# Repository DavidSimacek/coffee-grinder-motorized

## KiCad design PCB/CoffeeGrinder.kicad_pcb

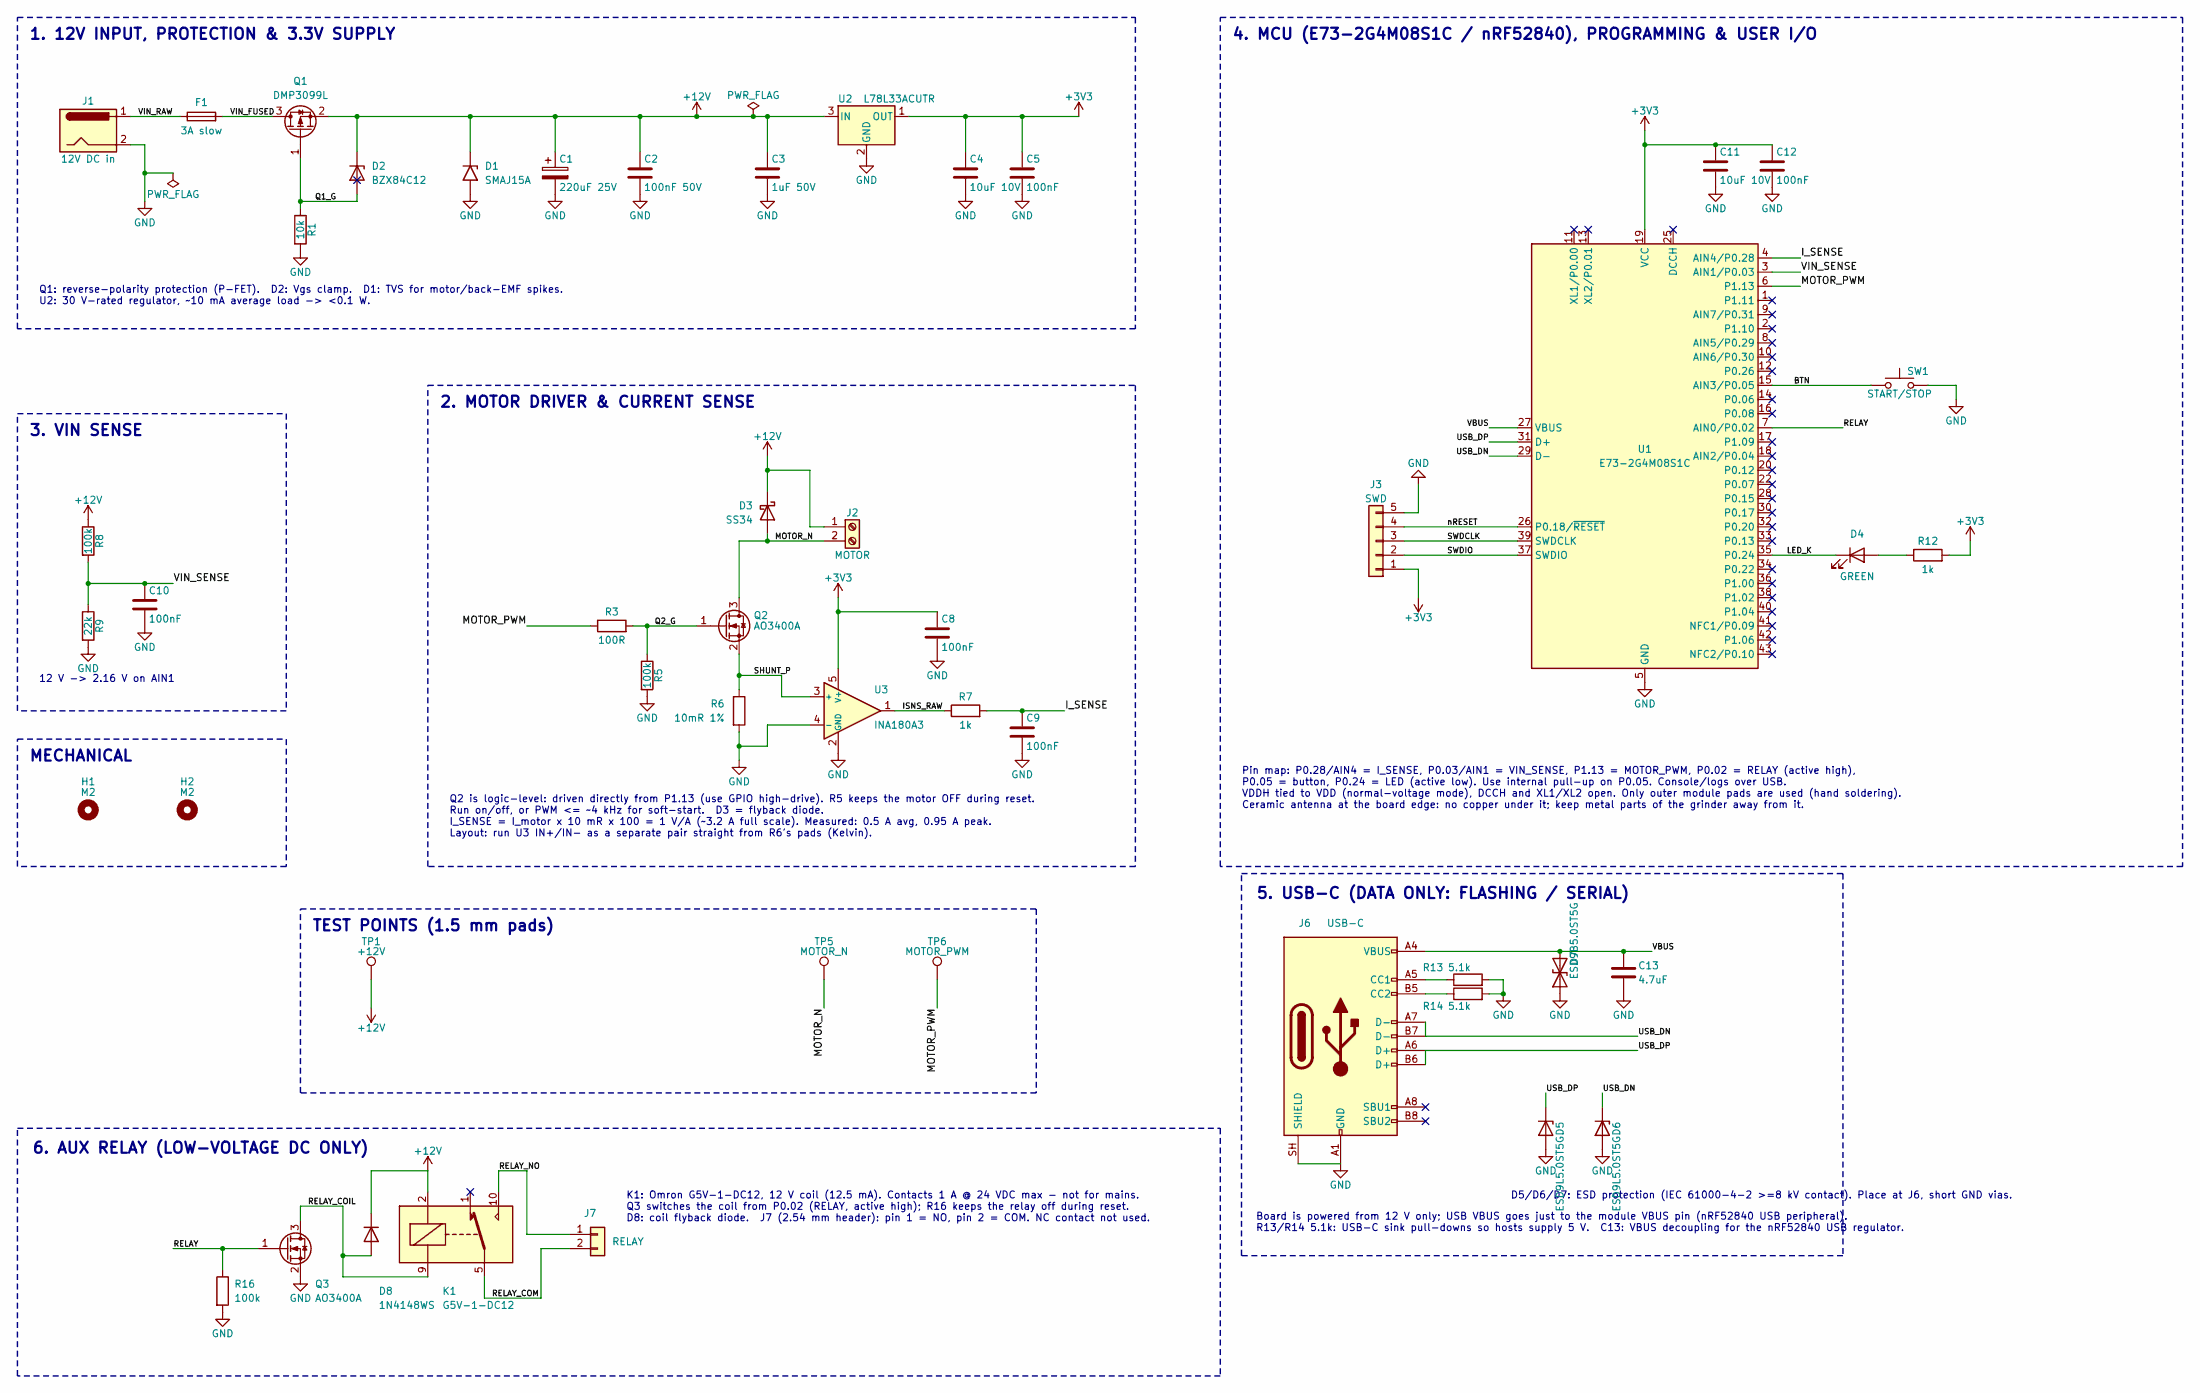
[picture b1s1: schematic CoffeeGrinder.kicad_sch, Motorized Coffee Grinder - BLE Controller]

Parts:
C1: 220uF 25V; CP_Radial_D6.3mm_P2.50mm
C2: 100nF 50V; C_0603_1608Metric
C3: 1uF 50V; C_0805_2012Metric
C4, C11: 10uF 10V; C_0805_2012Metric
C5, C8, C9, C10, C12: 100nF; C_0603_1608Metric
C13: 4.7uF; C_0603_1608Metric; LCSC C19666
D1: SMAJ15A; D_SMA
D2: BZX84C12; SOT-23
D3: SS34; D_SMA
D4: GREEN; LED_0603_1608Metric
D5, D6: ESD9L5.0ST5G; D_SOD-923_NoSilk; LCSC C82326
D7: ESD9B5.0ST5G; D_SOD-923_NoSilk; LCSC C111566
D8: 1N4148WS; D_SOD-323; LCSC C2128
F1: 3A slow; Fuse_1206_3216Metric; LCSC C41367225
H1, H2: M2; MountingHole_2.2mm_M2
J1: 12V DC in; BarrelJack_Horizontal
J2: MOTOR; TerminalBlock_Kefa_KF301-5.0-2P
J3: SWD; PinHeader_1x05_P2.54mm_Vertical
J6: USB-C; USB_C_HRO_TYPE-C-31-M-12_EdgeMount; LCSC C165948
J7: RELAY; PinHeader_1x02_P2.54mm_Vertical
K1: G5V-1-DC12; Relay_SPDT_Omron_G5V-1; LCSC C31113
Q1: DMP3099L; SOT-23
Q2: AO3400A; SOT-23
Q3: AO3400A; SOT-23; LCSC C20917
R1: 10k; R_0603_1608Metric
R3: 100R; R_0603_1608Metric
R5, R8: 100k; R_0603_1608Metric
R6: 10mR 1%; R_1206_3216Metric_Vishay_WSL
R7, R12: 1k; R_0603_1608Metric
R9: 22k; R_0603_1608Metric
R13, R14: 5.1k; R_0603_1608Metric; LCSC C23186
R16: 100k; R_0603_1608Metric; LCSC C25803
SW1: START/STOP; SW_PUSH_6mm_Drill1.3
TP1: +12V; TestPoint_Pad_D1.5mm
TP5: MOTOR_N; TestPoint_Pad_D1.5mm
TP6: MOTOR_PWM; TestPoint_Pad_D1.5mm
U1: E73-2G4M08S1C; MPN E73-2G4M08S1C; LCSC C356849
U2: L78L33ACUTR; SOT-89-3
U3: INA180A3; SOT-23-5

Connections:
+3V3: C4.1, C5.1, C8.1, C11.1, C12.1, J3.1, R12.2, U1.19 (VCC), U1.23 (VDDH), U2.1 (OUT), U3.5 (V+)
+12V: C1.1, C2.1, C3.1, D1.1 (A1), D2.3 (K), D3.1 (K), D8.1 (K), J2.1, K1.2, Q1.2 (S), R8.1, TP1.1 (1_1), U2.3 (IN)
/BTN: SW1.1, U1.15 (AIN3/P0.05)
/ISNS_RAW: R7.1, U3.1
/I_SENSE: C9.1, R7.2, U1.4 (AIN4/P0.28)
/LED_K: D4.1 (K), U1.35 (P0.24)
/MOTOR_N: D3.2 (A), J2.2, Q2.3 (D), TP5.1 (1_1)
/MOTOR_PWM: R3.1, TP6.1 (1_1), U1.6 (P1.13)
/Q1_G: D2.1 (A), Q1.1 (G), R1.1
/Q2_G: Q2.1 (G), R3.2, R5.1
/RELAY: Q3.1 (G), R16.1, U1.7 (AIN0/P0.02)
/RELAY_COIL: D8.2 (A), K1.9, Q3.3 (D)
/RELAY_COM: J7.2, K1.5, K1.6
/RELAY_NO: J7.1, K1.10
/SHUNT_P: Q2.2 (S), R6.1, U3.3 (+)
/SWDCLK: J3.3, U1.39 (SWDCLK)
/SWDIO: J3.2, U1.37 (SWDIO)
/USB_DN: D6.1 (K), J6.A7 (D-), J6.B7 (D-), U1.29 (D-)
/USB_DP: D5.1 (K), J6.A6 (D+), J6.B6 (D+), U1.31 (D+)
/VBUS: C13.1, D7.2 (A2), J6.A4 (VBUS), J6.A9 (VBUS), J6.B4 (VBUS), J6.B9 (VBUS), U1.27 (VBUS)
/VIN_FUSED: F1.2, Q1.3 (D)
/VIN_RAW: F1.1, J1.1
/VIN_SENSE: C10.1, R8.2, R9.1, U1.3 (AIN1/P0.03)
/nRESET: J3.4, U1.26 (P0.18/~RESET)
GND: C1.2, C2.2, C3.2, C4.2, C5.2, C8.2, C9.2, C10.2, C11.2, C12.2, C13.2, D1.2 (A2), D5.2 (A), D6.2 (A), D7.1 (A1), J1.2, J3.5, J6.A1 (GND), J6.A12 (GND), J6.B1 (GND), J6.B12 (GND), J6.SH (SHIELD), Q3.2 (S), R1.2, R5.2, R6.2, R9.2, R13.2, R14.2, R16.2, SW1.2, U1.5 (GND), U1.21 (GND), U1.24 (GND), U2.2 (GND), U3.2 (GND), U3.4 (-)
unnamed: D4.2 (A), R12.1
unnamed: J6.A5 (CC1), R13.1
unnamed: J6.B5 (CC2), R14.1

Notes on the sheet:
Pin map: P0.28/AIN4 = I_SENSE, P0.03/AIN1 = VIN_SENSE, P1.13 = MOTOR_PWM, P0.02 = RELAY (active high), P0.05 = button, P0.24 = LED (active low). Use internal pull-up on P0.05. Console/logs over USB. VDDH tied to VDD (normal-voltage mode), DCCH and XL1/XL2 open. Only outer module pads are used (hand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
Q2 is logic-level: driven directly from P1.13 (use GPIO high-drive). R5 keeps the motor OFF during reset. Run on/off, or PWM <= ~4 kHz for soft-start. D3 = flyback diode. I_SENSE = I_motor x 10 mR x 100 = 1 V/A (~3.2 A full scale). Measured: 0.5 A avg, 0.95 A peak. Layout: run U3 IN+/IN- as a separ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
MECHANICAL
TEST POINTS (1.5 mm pads)
12 V -> 2.16 V on AIN1
Q1: reverse-polarity protection (P-FET). D2: Vgs clamp. D1: TVS for motor/back-EMF spikes. U2: 30 V-rated regulator, ~10 mA average load -> <0.1 W.
3. VIN SENSE
2. MOTOR DRIVER & CURRENT SENSE
1. 12V INPUT, PROTECTION & 3.3V SUPPLY
4. MCU (E73-2G4M08S1C / nRF52840), PROGRAMMING & USER I/O
5. USB-C (DATA ONLY: FLASHING / SERIAL)
Board is powered from 12 V only; USB VBUS goes just to the module VBUS pin (nRF52840 USB peripheral). R13/R14 5.1k: USB-C sink pull-downs so hosts supply 5 V. C13: VBUS decoupling for the nRF52840 USB regulator.
D5/D6/D7: ESD protection (IEC 61000-4-2 >=8 kV contact). Place at J6, short GND vias.
6. AUX RELAY (LOW-VOLTAGE DC ONLY)
K1: Omron G5V-1-DC12, 12 V coil (12.5 mA). Contacts 1 A @ 24 VDC max - not for mains. Q3 switches the coil from P0.02 (RELAY, active high); R16 keeps the relay off during reset. D8: coil flyback diode. J7 (2.54 mm header): pin 1 = NO, pin 2 = COM. NC contact not used.

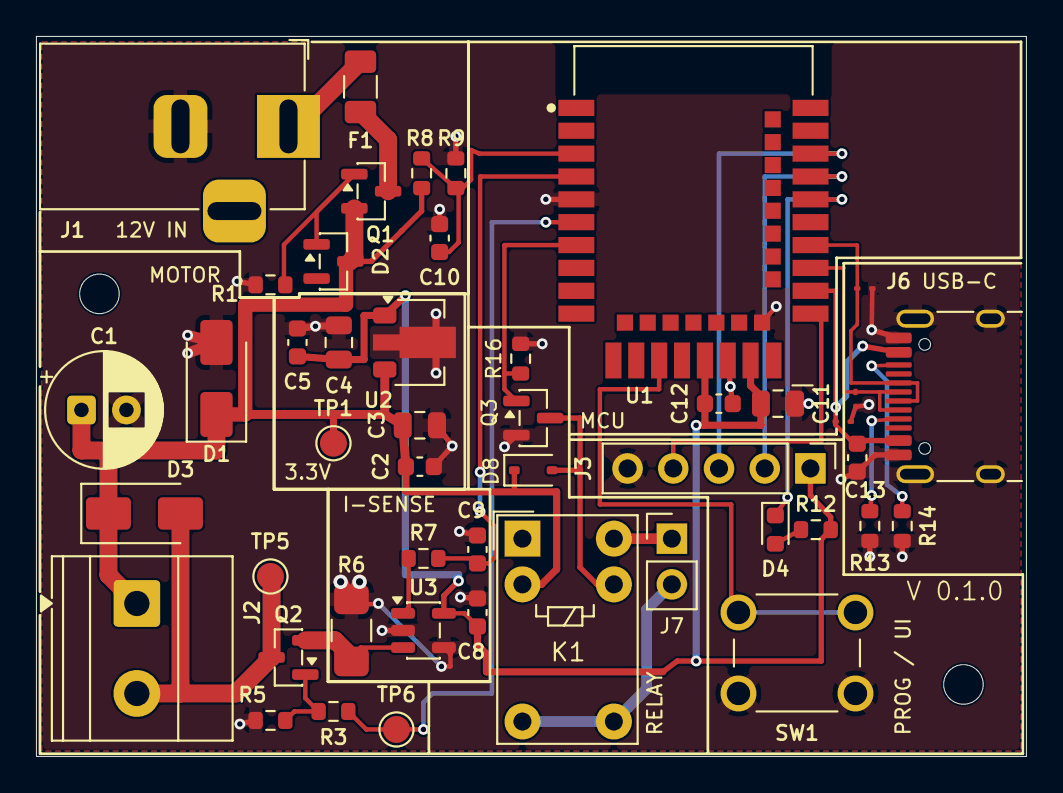
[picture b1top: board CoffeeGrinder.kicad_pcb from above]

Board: 2 copper layers, 55.0 x 40.0 mm, 49 parts (0 on the bottom side), 28 nets.

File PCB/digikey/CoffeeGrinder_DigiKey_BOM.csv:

Manufacturer Part Number,Manufacturer,Quantity,Customer Reference,Description
25YXJ220M6.3X11,Rubycon,1,C1,220uF 25V electrolytic radial 6.3mm P2.5mm
CL10B104KB8NNNC,Samsung,6,C2 C5 C8 C9 C10 C12,100nF 50V X7R 0603
CL21B105KBFNNNE,Samsung,1,C3,1uF 50V X7R 0805
CL21A106KAYNNNE,Samsung,2,C4 C11,10uF 25V X5R 0805
SMAJ15A,Littelfuse,1,D1,TVS 15V unidirectional SMA
BZX84C12LT1G,onsemi,1,D2,Zener 12V SOT-23
MBRA340T3G,onsemi,1,D3,Schottky 40V 3A SMA (flyback)
LTST-C191KGKT,Lite-On,1,D4,LED green 0603
0685T3000-01,Bel Fuse,1,F1,Fuse 3A slow-blow 1206
PJ-102AH,Same Sky (CUI),1,J1,DC barrel jack 5.5x2.1mm horizontal THT
1715022,Phoenix Contact,1,J2,"Screw terminal 2P 5.0mm (MKDS 1,5/2)"
PREC005SAAN-RC,Sullins,1,J3,Pin header 1x5 2.54mm
PREC004SAAN-RC,Sullins,1,J4,Pin header 1x4 2.54mm
B2B-PH-K-S(LF)(SN),JST,1,J5,JST PH 2-pin vertical header
DMP3099L-7,Diodes Inc,1,Q1,P-MOSFET 30V 3.8A SOT-23 (reverse polarity)
AO3400A,Alpha & Omega,1,Q2,N-MOSFET 30V 5.7A SOT-23 (motor switch)
RC0603FR-0710KL,Yageo,1,R1,10k 1% 0603
RC0603FR-07100RL,Yageo,1,R3,100R 1% 0603
RC0603FR-07100KL,Yageo,2,R5 R8,100k 1% 0603
WSLP1206R0100FEA,Vishay Dale,1,R6,10 mOhm 1% 1206 current sense
RC0603FR-071KL,Yageo,2,R7 R12,1k 1% 0603
RC0603FR-0722KL,Yageo,1,R9,22k 1% 0603
B3F-1000,Omron,1,SW1,Tactile switch 6x6mm THT
L78L33ACUTR,STMicroelectronics,1,U2,"3.3V 100mA regulator, 30V in, SOT-89"
INA180A3IDBVR,Texas Instruments,1,U3,"Current sense amp, gain 100, SOT-23-5"

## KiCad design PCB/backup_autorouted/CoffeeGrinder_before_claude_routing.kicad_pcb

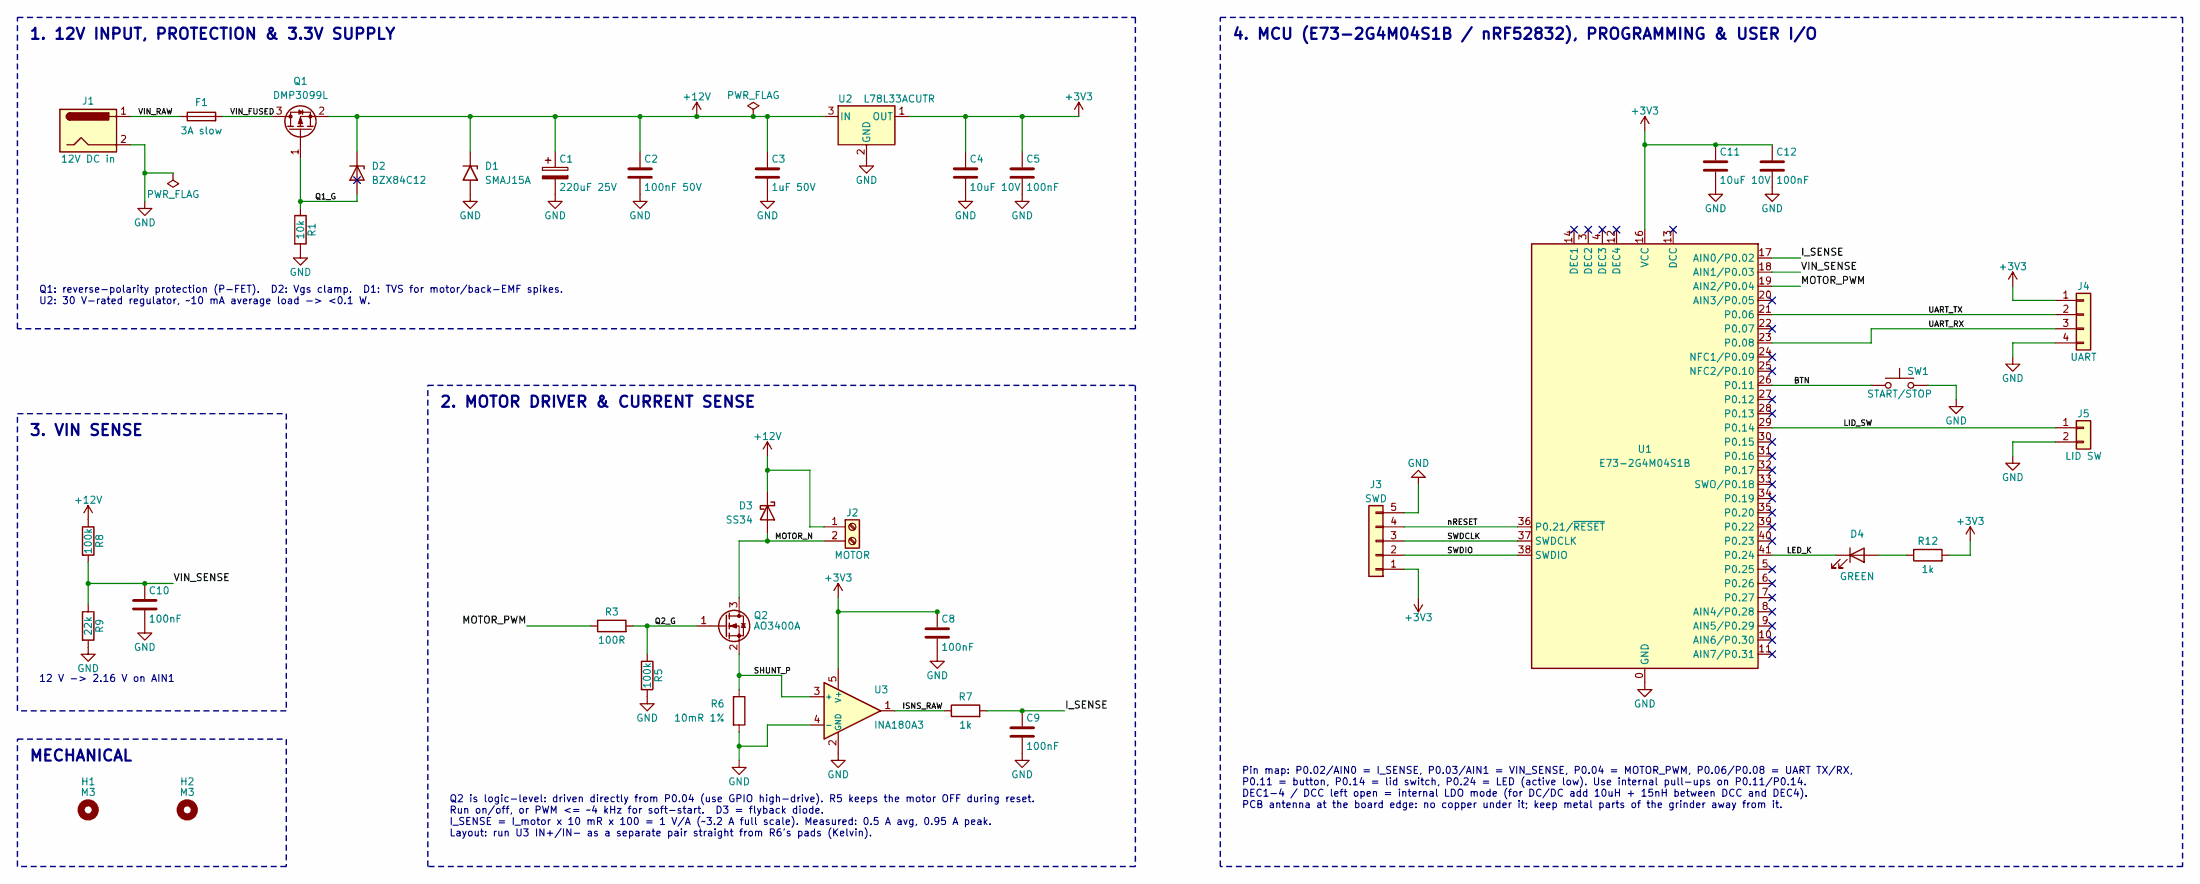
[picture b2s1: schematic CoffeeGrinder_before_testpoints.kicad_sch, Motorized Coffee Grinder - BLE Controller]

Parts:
C1: 220uF 25V; CP_Radial_D6.3mm_P2.50mm
C2: 100nF 50V; C_0603_1608Metric
C3: 1uF 50V; C_0805_2012Metric
C4, C11: 10uF 10V; C_0805_2012Metric
C5, C8, C9, C10, C12: 100nF; C_0603_1608Metric
D1: SMAJ15A; D_SMA
D2: BZX84C12; SOT-23
D3: SS34; D_SMA
D4: GREEN; LED_0603_1608Metric
F1: 3A slow; Fuse_1206_3216Metric; LCSC C41367225
H1, H2: M3; MountingHole_3.2mm_M3
J1: 12V DC in; BarrelJack_Horizontal
J2: MOTOR; TerminalBlock_Phoenix_MKDS-1,5-2_1x02_P5.00mm_Horizontal
J3: SWD; PinHeader_1x05_P2.54mm_Vertical
J4: UART; PinHeader_1x04_P2.54mm_Vertical
J5: LID SW; JST_PH_B2B-PH-K_1x02_P2.00mm_Vertical
Q1: DMP3099L; SOT-23
Q2: AO3400A; SOT-23
R1: 10k; R_0603_1608Metric
R3: 100R; R_0603_1608Metric
R5, R8: 100k; R_0603_1608Metric
R6: 10mR 1%; R_1206_3216Metric
R7, R12: 1k; R_0603_1608Metric
R9: 22k; R_0603_1608Metric
SW1: START/STOP; SW_PUSH_6mm
U1: E73-2G4M04S1B; E73-2G4M04S; MPN E73-2G4M04S1B; LCSC C411306
U2: L78L33ACUTR; SOT-89-3
U3: INA180A3; SOT-23-5

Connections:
+3V3: C4.1, C5.1, C8.1, C11.1, C12.1, J3.1, J4.1, R12.2, U1.16 (VCC), U2.1 (OUT), U3.5 (V+); also elsewhere on the board
+12V: C1.1, C2.1, C3.1, D1.1 (A1), D2.3 (K), D3.1 (K), J2.1, Q1.2 (S), R8.1, U2.3 (IN); also elsewhere on the board
/BTN: SW1.1, U1.26 (P0.11)
/ISNS_RAW: R7.1, U3.1
/I_SENSE: C9.1, R7.2, U1.17 (AIN0/P0.02); also elsewhere on the board
/LED_K: D4.1 (K), U1.41 (P0.24)
/LID_SW: J5.1, U1.29 (P0.14)
/MOTOR_N: D3.2 (A), J2.2, Q2.3 (D); also elsewhere on the board
/MOTOR_PWM: R3.1, U1.19 (AIN2/P0.04); also elsewhere on the board
/Q1_G: D2.1 (A), Q1.1 (G), R1.1
/Q2_G: Q2.1 (G), R3.2, R5.1
/SHUNT_P: Q2.2 (S), R6.1, U3.3 (+)
/SWDCLK: J3.3, U1.37 (SWDCLK)
/SWDIO: J3.2, U1.38 (SWDIO)
/UART_RX: J4.3, U1.23 (P0.08)
/UART_TX: J4.2, U1.21 (P0.06)
/VIN_FUSED: F1.2, Q1.3 (D)
/VIN_RAW: F1.1, J1.1
/VIN_SENSE: C10.1, R8.2, R9.1, U1.18 (AIN1/P0.03)
/nRESET: J3.4, U1.36 (P0.21/~RESET)
GND: C1.2, C2.2, C3.2, C4.2, C5.2, C8.2, C9.2, C10.2, C11.2, C12.2, D1.2 (A2), J1.2, J3.5, J4.4, J5.2, R1.2, R5.2, R6.2, R9.2, SW1.2, U1.0 (GND), U1.1 (GND), U1.2 (GND), U1.15 (GND), U1.42 (GND), U1.43 (GND), U2.2 (GND), U3.2 (GND), U3.4 (-); also elsewhere on the board
unnamed: D4.2 (A), R12.1

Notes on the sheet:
1. 12V INPUT, PROTECTION & 3.3V SUPPLY
Q1: reverse-polarity protection (P-FET). D2: Vgs clamp. D1: TVS for motor/back-EMF spikes. U2: 30 V-rated regulator, ~10 mA average load -> <0.1 W.
2. MOTOR DRIVER & CURRENT SENSE
Q2 is logic-level: driven directly from P0.04 (use GPIO high-drive). R5 keeps the motor OFF during reset. Run on/off, or PWM <= ~4 kHz for soft-start. D3 = flyback diode. I_SENSE = I_motor x 10 mR x 100 = 1 V/A (~3.2 A full scale). Measured: 0.5 A avg, 0.95 A peak. Layout: run U3 IN+/IN- as a separ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
3. VIN SENSE
12 V -> 2.16 V on AIN1
MECHANICAL
4. MCU (E73-2G4M04S1B / nRF52832), PROGRAMMING & USER I/O
Pin map: P0.02/AIN0 = I_SENSE, P0.03/AIN1 = VIN_SENSE, P0.04 = MOTOR_PWM, P0.06/P0.08 = UART TX/RX, P0.11 = button, P0.14 = lid switch, P0.24 = LED (active low). Use internal pull-ups on P0.11/P0.14. DEC1-4 / DCC left open = internal LDO mode (for DC/DC add 10uH + 15nH between DCC and DEC4). PCB an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

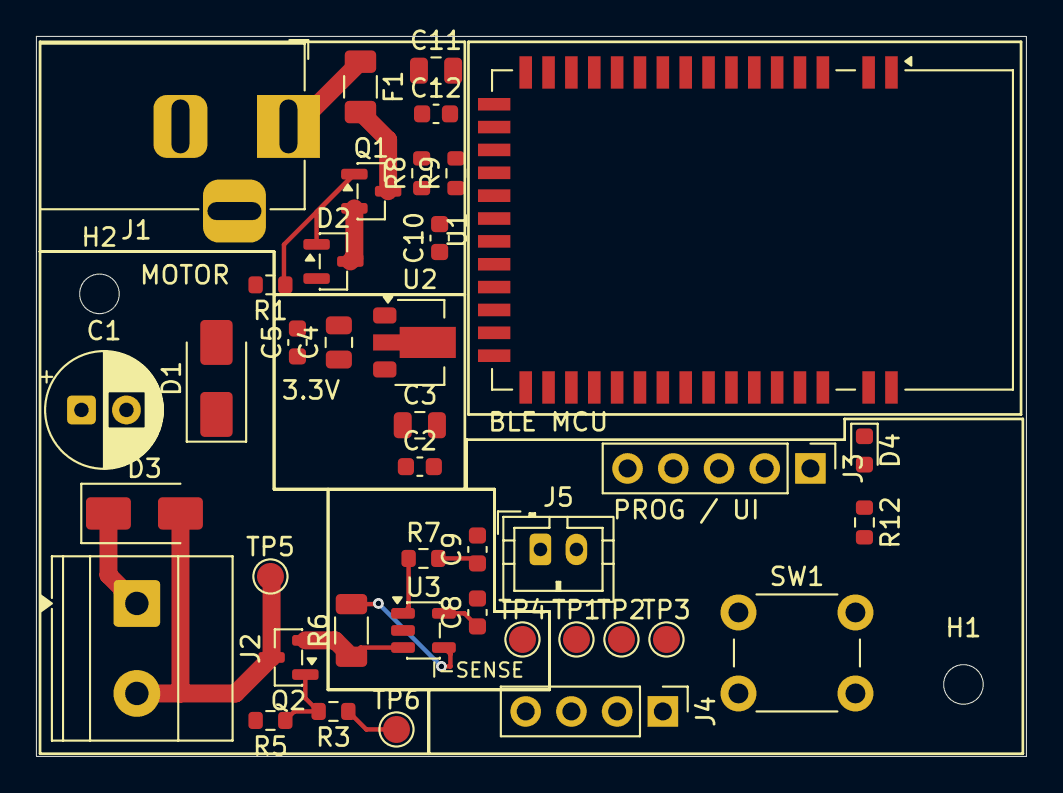
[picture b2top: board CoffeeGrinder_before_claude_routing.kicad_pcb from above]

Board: 2 copper layers, 55.0 x 40.0 mm, 42 parts (0 on the bottom side), 22 nets.

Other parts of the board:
TP1: +12V; TestPoint_Pad_D1.5mm
TP2: +3V3; TestPoint_Pad_D1.5mm
TP3: GND; TestPoint_Pad_D1.5mm
TP4: I_SENSE; TestPoint_Pad_D1.5mm
TP5: MOTOR_N; TestPoint_Pad_D1.5mm
TP6: MOTOR_PWM; TestPoint_Pad_D1.5mm

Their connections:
+3V3: TP2.1 (1_1); also elsewhere on the board
+12V: TP1.1 (1_1); also elsewhere on the board
/I_SENSE: TP4.1 (1_1); also elsewhere on the board
/MOTOR_N: TP5.1 (1_1); also elsewhere on the board
/MOTOR_PWM: TP6.1 (1_1); also elsewhere on the board
GND: TP3.1 (1_1); also elsewhere on the board

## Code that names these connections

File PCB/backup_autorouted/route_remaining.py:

"""Route the remaining CoffeeGrinder nets on top of the user's placement.
usage: python.exe route.py <in.kicad_pcb> <out.kicad_pcb>
"""
import sys
import pcbnew

b = pcbnew.LoadBoard(sys.argv[1])
MM = pcbnew.FromMM
F, B = pcbnew.F_Cu, pcbnew.B_Cu
nets = b.GetNetsByName()


def net(name):
    n = nets[name]
    assert n is not None and n.GetNetCode() > 0, name
    return n


def P(x, y):
    return pcbnew.VECTOR2I(MM(x), MM(y))


def path(netname, layer, width, pts):
    for a, c in zip(pts, pts[1:]):
        t = pcbnew.PCB_TRACK(b)
        t.SetStart(P(*a)); t.SetEnd(P(*c))
        t.SetWidth(MM(width)); t.SetLayer(layer); t.SetNet(net(netname))
        b.Add(t)


def via(netname, x, y, d=0.6, drill=0.3):
    v = pcbnew.PCB_VIA(b)
    v.SetPosition(P(x, y)); v.SetWidth(MM(d)); v.SetDrill(MM(drill))
    v.SetLayerPair(F, B); v.SetNet(net(netname))
    b.Add(v)


# ---------------- +12V ----------------
# main bus D2/Q1 -> past R1 -> down beside D1 -> D1 K   (0.8 mm: channel between R1 and C4/C5)
path('+12V', F, 0.8, [(67.438, 74.5), (67.2, 74.74), (67.2, 76.9), (61.6, 76.9), (61.6, 83.0), (60.0, 83.0)])
# D1 K -> C1+ and D3 K (motor supply, 1.0 mm)
path('+12V', F, 1.0, [(60.0, 83.0), (60.0, 85.0), (54.0, 85.0), (54.0, 88.5)])
path('+12V', F, 1.0, [(54.0, 85.0), (52.5, 85.0), (52.5, 82.75)])
# regulator branch: bus -> U2 pin 3, C3, C2 (0.5 mm)
path('+12V', F, 0.5, [(61.6, 83.0), (69.35, 83.0), (70.35, 83.6)])
path('+12V', F, 0.5, [(69.35, 83.0), (69.35, 80.5)])
path('+12V', F, 0.5, [(70.35, 83.6), (70.525, 85.9)])
# divider top R8 pad 1
path('+12V', F, 0.3, [(67.438, 74.5), (68.6, 74.5), (70.3, 72.8), (71.4, 71.7), (71.4, 70.425)])
# TP1 from C2
path('+12V', F, 0.4, [(70.525, 85.9), (70.525, 87.3), (76.6, 87.3), (76.6, 92.6), (78.8, 92.6), (80.0, 93.8), (80.0, 95.5)])

# ---------------- +3V3 ----------------
path('+3V3', F, 0.4, [(69.35, 77.5), (68.2, 77.5), (68.2, 79.95), (66.8, 79.95), (64.5, 79.775)])
# up to the module: B.Cu jumper U2 -> C12
via('+3V3', 70.5, 76.4)
path('+3V3', F, 0.4, [(70.5, 76.4), (69.35, 77.5)])
via('+3V3', 70.5, 66.3)
path('+3V3', B, 0.4, [(70.5, 76.4), (70.5, 66.3)])
path('+3V3', F, 0.4, [(70.5, 66.3), (71.425, 66.3)])
path('+3V3', F, 0.4, [(75.43, 65.765), (74.3, 65.765), (73.85, 65.22), (71.425, 65.22), (71.425, 66.3)])
path('+3V3', F, 0.4, [(71.425, 65.22), (71.25, 64.62), (71.25, 63.9)])
# down to U3/C8: B.Cu jumper
path('+3V3', B, 0.4, [(70.5, 76.4), (70.5, 91.9), (73.45, 91.9), (73.45, 92.25)])
via('+3V3', 73.45, 92.25)
path('+3V3', F, 0.3, [(73.45, 92.25), (72.638, 93.06), (72.638, 94.05)])
# C8 -> TP2 -> J4 pin 1
path('+3V3', F, 0.4, [(74.5, 94.775), (74.5, 95.8), (75.0, 96.3), (75.0, 97.3), (84.8, 97.3), (84.8, 99.5)])
path('+3V3', F, 0.4, [(82.5, 97.3), (82.5, 95.5)])
# J4 pin 1 -> J3 pin 1 on B.Cu (both THT)
path('+3V3', B, 0.4, [(84.8, 99.5), (86.7, 97.6), (86.7, 89.3), (93.0, 89.3), (93.0, 86.0)])
# R12 -> J3 pin 1
path('+3V3', F, 0.3, [(96.0, 89.825), (94.6, 89.825), (93.0, 88.225), (93.0, 86.0)])

# ---------------- VIN_SENSE ----------------
path('/VIN_SENSE', F, 0.25, [(71.4, 68.775), (73.3, 70.425)])
path('/VIN_SENSE', F, 0.25, [(73.3, 70.425), (73.45, 70.575), (73.45, 73.45), (72.925, 73.975), (72.4, 73.975)])
path('/VIN_SENSE', F, 0.25, [(75.43, 68.305), (74.15, 68.305), (74.15, 69.95), (73.68, 70.425), (73.3, 70.425)])

# ---------------- module left-side signals: vias inboard, B.Cu lanes ----------------
# I_SENSE  (pin 17) lane x=75.1 -> via near C9 -> C9 pin 1 and TP4
via('/I_SENSE', 77.0, 67.035)
path('/I_SENSE', F, 0.25, [(75.43, 67.035), (77.0, 67.035)])
path('/I_SENSE', B, 0.25, [(77.0, 67.035), (75.1, 67.035), (75.1, 87.9), (74.8, 88.2)])
via('/I_SENSE', 74.8, 88.2)
path('/I_SENSE', F, 0.25, [(74.8, 88.2), (75.5, 88.9), (75.5, 90.9), (75.125, 91.275), (74.5, 91.275)])
path('/I_SENSE', F, 0.25, [(75.5, 90.9), (75.5, 94.0), (76.4, 94.9), (77.0, 95.5)])
# MOTOR_PWM (pin 19) lane x=75.65 -> via next to TP6
via('/MOTOR_PWM', 77.0, 69.575)
path('/MOTOR_PWM', F, 0.25, [(75.43, 69.575), (77.0, 69.575)])
path('/MOTOR_PWM', B, 0.25, [(77.0, 69.575), (75.65, 69.575), (75.65, 98.5), (72.0, 98.5), (71.5, 99.0), (71.5, 100.5)])
via('/MOTOR_PWM', 71.5, 100.5)
path('/MOTOR_PWM', F, 0.25, [(71.5, 100.5), (70.0, 100.5)])
# UART_RX (pin 23) lane x=76.2 -> J4 pin 3 (THT)
via('/UART_RX', 77.0, 74.655)
path('/UART_RX', F, 0.25, [(75.43, 74.655), (77.0, 74.655)])
path('/UART_RX', B, 0.25, [(77.0, 74.655), (76.2, 74.655), (76.2, 97.0), (79.72, 97.0), (79.72, 99.5)])
# UART_TX (pin 21) east lane x=81.3 between J5 and J3 -> J4 pin 2 (THT)
via('/UART_TX', 77.0, 72.115)
path('/UART_TX', F, 0.25, [(75.43, 72.115), (77.0, 72.115)])
path('/UART_TX', B, 0.25, [(77.0, 72.115), (81.3, 72.115), (81.3, 97.5), (82.26, 98.46), (82.26, 99.5)])
# LID_SW (pin 29) on B.Cu straight down to J5 pin 1 (THT)
via('/LID_SW', 78.45, 79.95)
path('/LID_SW', F, 0.25, [(78.45, 81.5), (78.45, 79.95)])
path('/LID_SW', B, 0.25, [(78.45, 79.95), (78.45, 89.6), (78.0, 90.05), (78.0, 90.5)])
# BTN (pin 26) on F.Cu: through the U2/module gap, under the module edge, between J5 and J3
path('/BTN', F, 0.25, [(75.43, 78.465), (74.0, 78.465), (74.0, 83.3), (80.5, 83.3), (81.25, 84.05),
                       (81.25, 92.5), (87.5, 92.5), (89.0, 94.0)])
path('/BTN', F, 0.25, [(89.0, 94.0), (95.5, 94.0)])

# ---------------- SWD / LED ----------------
path('/nRESET', F, 0.25, [(87.34, 81.5), (87.34, 83.5), (85.38, 85.46), (85.38, 86.0)])
path('/SWDCLK', F, 0.25, [(88.61, 81.5), (88.61, 85.31), (87.92, 86.0)])
path('/SWDIO', F, 0.25, [(89.88, 81.5), (89.88, 85.42), (90.46, 86.0)])
path('/LED_K', F, 0.25, [(93.69, 81.5), (93.69, 82.6), (95.3, 84.213), (96.0, 84.213)])
path('Net-(D4-A)', F, 0.25, [(96.0, 85.787), (96.0, 88.175)])

# ---------------- GND stitching to the bottom plane ----------------
path('GND', F, 0.4, [(73.15, 63.9), (77.18, 64.0)])                  # C11 -> module GND pin 15
path('GND', F, 0.3, [(73.3, 68.775), (73.3, 67.55), (72.975, 66.3)])  # R9 -> C12 GND
via('GND', 73.3, 67.55)
via('GND', 72.4, 71.6); path('GND', F, 0.3, [(72.4, 71.6), (72.4, 72.425)])          # C10
via('GND', 65.5, 78.1); path('GND', F, 0.4, [(64.5, 78.225), (65.5, 78.1), (66.8, 78.05)])  # C5/C4
via('GND', 61.15, 75.6); path('GND', F, 0.3, [(61.15, 75.6), (62.175, 75.8)])        # R1
via('GND', 58.4, 78.6); via('GND', 58.4, 79.6)                                    # D1 anode
path('GND', F, 0.6, [(58.4, 78.6), (60.0, 79.0), (58.4, 79.6)])
via('GND', 72.2, 77.4); via('GND', 72.2, 80.7)                                    # U2 tab
path('GND', F, 0.4, [(72.2, 77.4), (72.2, 79.0), (72.2, 80.7)])
via('GND', 73.1, 84.75); path('GND', F, 0.3, [(72.25, 83.6), (73.1, 84.75), (72.075, 85.9)])  # C3/C2
via('GND', 73.5, 89.5); path('GND', F, 0.3, [(73.5, 89.5), (74.5, 89.725)])          # C9
via('GND', 73.55, 93.15); path('GND', F, 0.3, [(74.5, 93.225), (73.55, 93.15)])      # C8
via('GND', 69.2, 95.0); path('GND', F, 0.3, [(70.362, 95.0), (69.2, 95.0)])          # U3 GND
via('GND', 61.3, 100.2); path('GND', F, 0.3, [(62.175, 100.0), (61.3, 100.2)])       # R5
via('GND', 66.9, 92.3, 0.8, 0.4); via('GND', 67.95, 92.3, 0.8, 0.4)              # shunt return
path('GND', F, 0.8, [(66.9, 92.3), (67.5, 93.537), (67.95, 92.3)])
via('GND', 85.0, 93.9); path('GND', F, 0.3, [(85.0, 93.9), (85.0, 95.5)])            # TP3
via('GND', 77.18, 65.5)                                                           # module pin 15
via('GND', 96.23, 80.0); via('GND', 97.5, 80.0)                                   # module pins 42/43
path('GND', F, 0.3, [(96.23, 81.5), (96.23, 80.0)]); path('GND', F, 0.3, [(97.5, 81.5), (97.5, 80.0)])
via('GND', 93.69, 65.5); via('GND', 96.23, 65.5)                                  # module pins 2/1
path('GND', F, 0.3, [(93.69, 64.0), (93.69, 65.5)]); path('GND', F, 0.3, [(96.23, 64.0), (96.23, 65.5)])
path('GND', F, 0.3, [(96.23, 64.0), (97.5, 64.0)])

# ---------------- GND pours, both layers ----------------
for layer, prio in ((B, 0), (F, 0)):
    z = pcbnew.ZONE(b)
    z.SetLayer(layer); z.SetNet(net('GND'))
    z.SetAssignedPriority(prio)
    z.SetLocalClearance(MM(0.3))
    z.SetMinThickness(MM(0.25))
    z.SetThermalReliefGap(MM(0.4))
    z.SetThermalReliefSpokeWidth(MM(0.5))
    z.SetPadConnection(pcbnew.ZONE_CONNECTION_THERMAL)
    z.SetIslandRemovalMode(pcbnew.ISLAND_REMOVAL_MODE_ALWAYS)
    o = z.Outline(); o.NewOutline()
    for x, y in ((50.3, 62.3), (104.7, 62.3), (104.7, 101.7), (50.3, 101.7)):
        o.Append(MM(x), MM(y))
    b.Add(z)

pcbnew.ZONE_FILLER(b).Fill(b.Zones())
b.Save(sys.argv[2])
print('saved', sys.argv[2])
